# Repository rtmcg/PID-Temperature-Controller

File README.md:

# PHYS-339
Code and hardware schematics for the the new PID temperature controller lab in the Physics 339 laboratory course at McGill university.

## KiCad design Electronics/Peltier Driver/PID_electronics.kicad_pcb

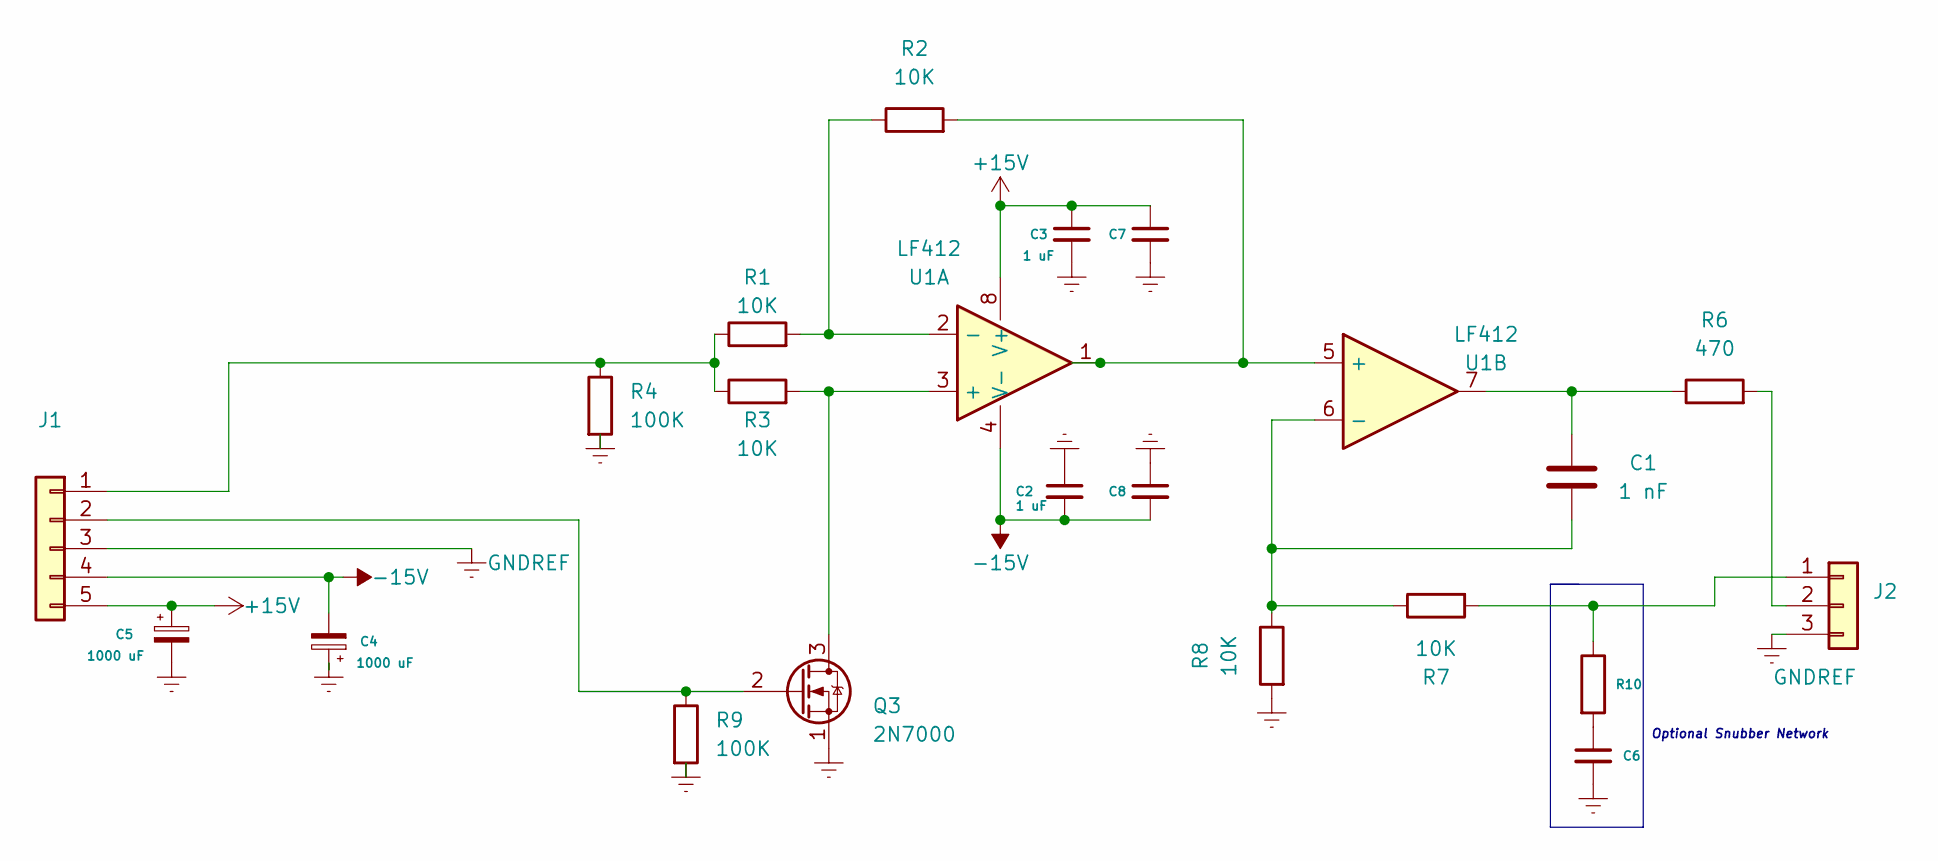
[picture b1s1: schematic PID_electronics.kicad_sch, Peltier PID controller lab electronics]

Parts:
C1: 1 nF; C_Axial_L3.8mm_D2.6mm_P7.50mm_Horizontal
C2, C3: 1 uF; C_Axial_L3.8mm_D2.6mm_P7.50mm_Horizontal
C4, C5: 1000 uF; CP_Radial_D10.0mm_P5.00mm
C6: C_Small; CP_Radial_D10.0mm_P5.00mm
C7, C8: C_Small; C_Axial_L3.8mm_D2.6mm_P7.50mm_Horizontal
J1: Conn_01x05; 1935190
J2: Conn_01x03; 1935174
Q3: 2N7000; TO-92_HandSolder
R1, R2, R3, R7, R8: 10K; R_Axial_DIN0207_L6.3mm_D2.5mm_P10.16mm_Horizontal
R4, R9: 100K; R_Axial_DIN0207_L6.3mm_D2.5mm_P10.16mm_Horizontal
R6: 470; R_Axial_DIN0207_L6.3mm_D2.5mm_P10.16mm_Horizontal
R10: R; R_Axial_DIN0207_L6.3mm_D2.5mm_P10.16mm_Horizontal
U1: LF412; DIP-8_W7.62mm_Socket_LongPads

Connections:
+15V: C3.1, C5.1, C7.1, J1.5, U1.8 (V+)
-15V: C2.2, C4.2, C8.2, J1.4, U1.4 (V-)
GNDREF: C2.1, C3.2, C4.1, C5.2, C6.2, C7.2, C8.1, J1.3, J2.3, Q3.1 (S), R4.2, R8.2, R9.2
unnamed: C1.1, R6.1, U1.7
unnamed: C1.2, R7.1, R8.1, U1.6 (-)
unnamed: J2.1, R7.2, R10.1
unnamed: J2.2, R6.2
unnamed: J1.2, Q3.2 (G), R9.1
unnamed: Q3.3 (D), R3.2, U1.3 (+)
unnamed: J1.1, R1.1, R3.1, R4.1
unnamed: R1.2, R2.1, U1.2 (-)
unnamed: R2.2, U1.1, U1.5 (+)
unnamed: C6.1, R10.2

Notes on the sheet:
Optional Snubber Network

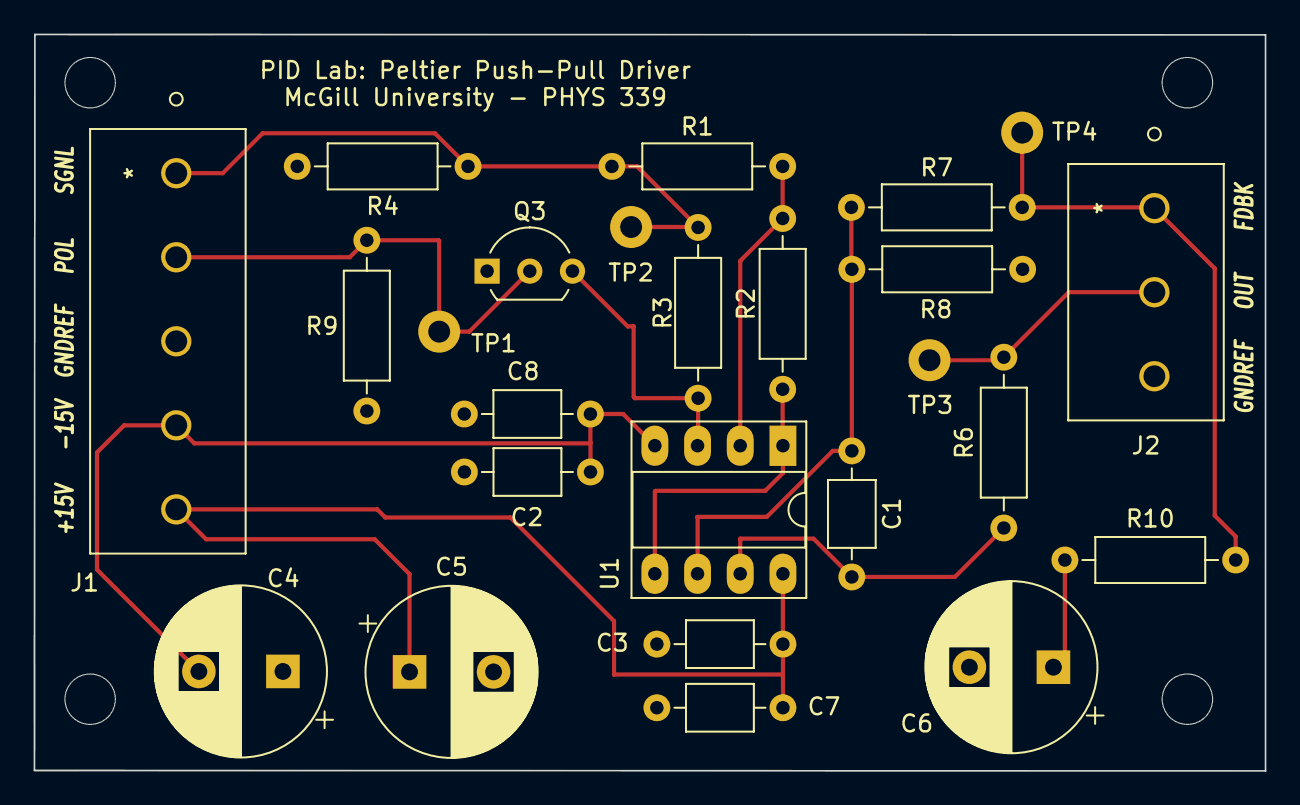
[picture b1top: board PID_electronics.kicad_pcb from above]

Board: 2 copper layers, 73.2 x 43.8 mm, 21 parts (0 on the bottom side), 13 nets.

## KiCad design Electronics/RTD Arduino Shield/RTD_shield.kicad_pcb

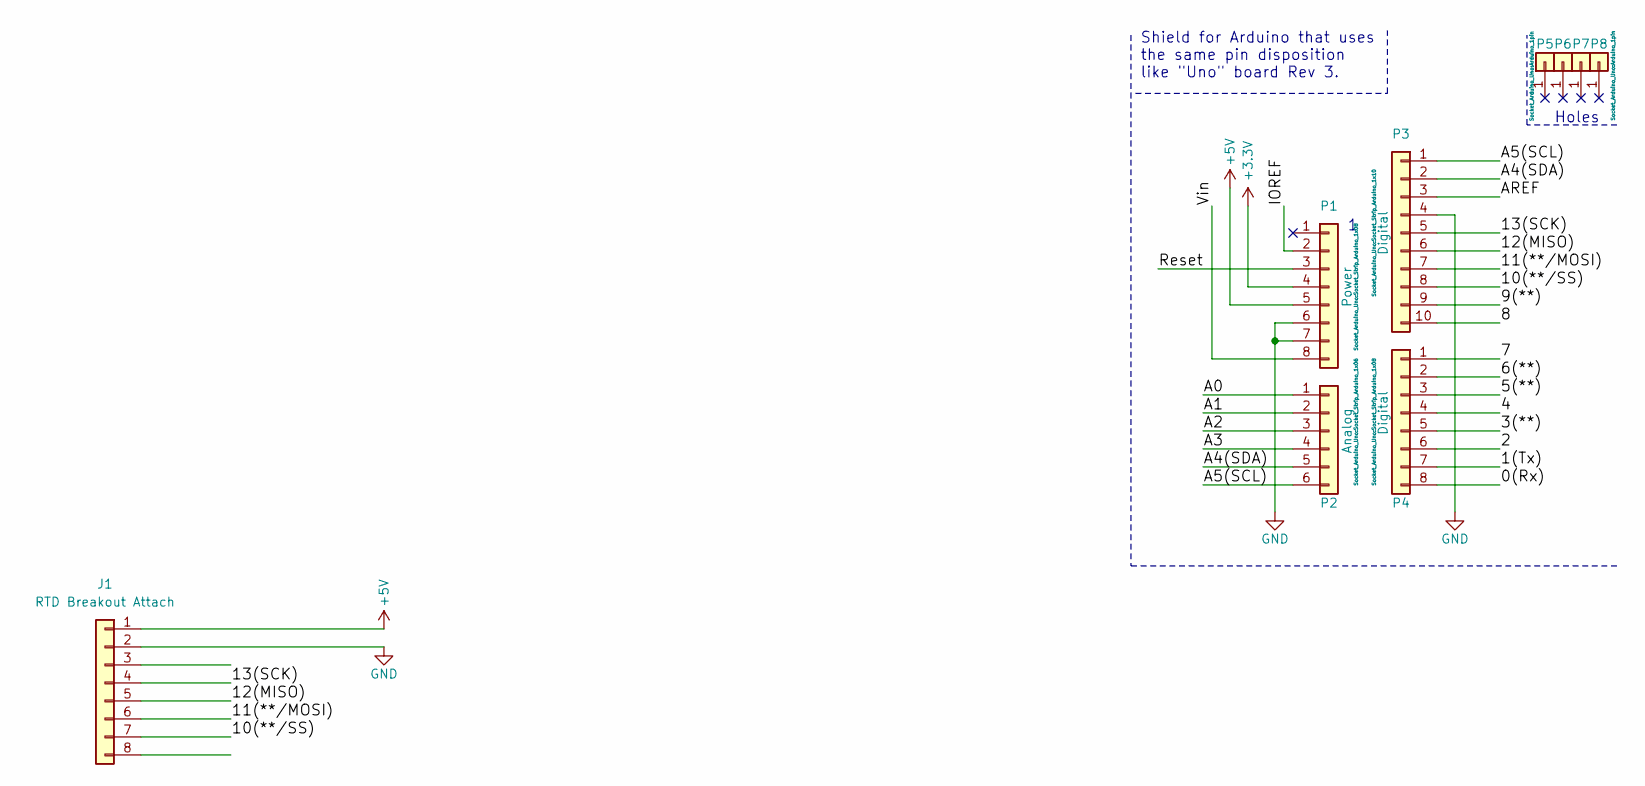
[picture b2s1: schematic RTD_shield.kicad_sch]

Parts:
J1: RTD Breakout Attach; Socket_Strip_Arduino_1x08
P1: Power; Socket_Strip_Arduino_1x08
P2: Analog; Socket_Strip_Arduino_1x06
P3: Digital; Socket_Strip_Arduino_1x10
P4: Digital; Socket_Strip_Arduino_1x08
P5, P6, P7, P8: CONN_01X01; Arduino_1pin

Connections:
+3V3: P1.4
+5V: J1.1, P1.5
/0(Rx): P4.8
/1(Tx): P4.7
/2: P4.6
/3(**): P4.5
/4: P4.4
/5(**): P4.3
/6(**): P4.2
/7: P4.1
/8: P3.10
/9(**): P3.9
/10(**/SS): J1.7, P3.8
/11(**/MOSI): J1.6, P3.7
/12(MISO): J1.5, P3.6
/13(SCK): J1.4, P3.5
/A0: P2.1
/A1: P2.2
/A2: P2.3
/A3: P2.4
/A4(SDA): P2.5, P3.2
/A5(SCL): P2.6, P3.1
/AREF: P3.3
/IOREF: P1.2
/Reset: P1.3
/Vin: P1.8
GND: J1.2, P1.6, P1.7, P3.4

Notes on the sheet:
Holes
Shield for Arduino that uses the same pin disposition like "Uno" board Rev 3.

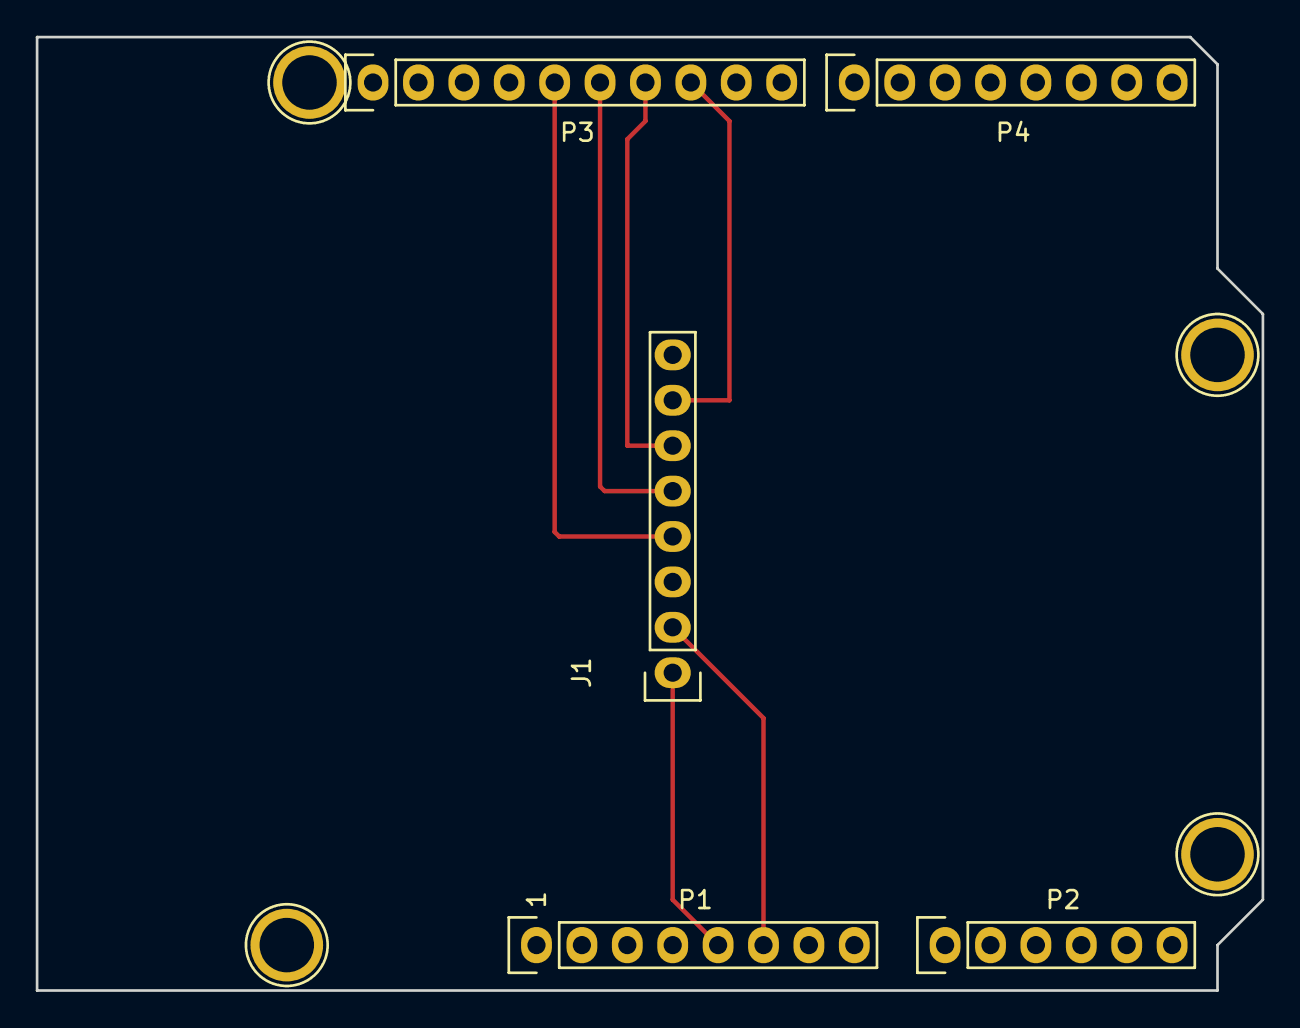
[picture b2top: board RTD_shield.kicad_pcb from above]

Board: 2 copper layers, 68.6 x 53.3 mm, 9 parts (0 on the bottom side), 8 nets.

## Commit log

2021-09-30 Improving Documentation and removing redundancy
2021-09-30 File change
2021-09-30 Deleted a file
2021-09-30 Fixed data line problems, improved debug
2021-10-07 small changes
2021-10-13 Removing old code for a new implementation
2021-10-13 New implementation of arduino api and GUI based on mcphysics auber controller.
2021-10-13 Arduino Code begins
2021-10-13 Adding serial functionality
2021-10-13 Adding functionality
2021-10-14 Integrating arduino code and python api.
2021-10-14 minor changes
2021-10-14 Fixing problems and adding functionality to all program components
2021-10-18 Fixed simulation in the GUI
2021-10-18 broad additions
2021-10-29 Api and arduino code fixes
2021-11-11 Major updates across the board
2021-11-18 Added functionality on both GUI and arduino side.
2021-11-19 breaking up arduino.py
2021-11-19 Broke up arduino.py into api and gui scripts.
2021-11-19 Moving toward a functioning version
2021-11-19 Modifed read_temperature()
2021-11-29 Added RTD temperature measurement (MAX31865 ic)
2021-12-02 Stable in open and closed loop operation.
2021-12-03 Added functionality for changing control period from gui and a single function to get all parameters from arduino to the api (get_all_variables) to simplify querying of the arduino.
2021-12-03 minor updates
2021-12-07 Added variables and math for calculating dt, the time differential needed for the control function.
2021-12-07 Removed the GUI window population code from init to clean up the code, added provision from automatically finding arduino serial port.
2022-01-11 CAD files for supporting electronics
2022-01-12 Test Arduino shield for RTD breakout board
2022-01-12 Terminal block footprints
2022-01-12 File reorganization
2022-01-12 File reorg
2022-01-12 photos for the wiki
2022-01-12 photos
2022-01-13 Combined schematic of 3 electronics blocks
2022-01-13 Combined schematic of 3 electronics blocks (minor change)
2022-01-14 updated silkscreen
2022-01-14 Components for PCB construction
2022-01-14 schematic image added
2022-01-14 Gerber files for PCB production
2022-01-20 Image of data acquisition in the gui added
2022-01-21 Added mounting holes
2022-01-21 mounting hole footprint
2022-01-24 Board revision
2022-01-31 Added Bulk decoupling capacitors and optional snubber network
2022-02-01 Have to add changes
2022-02-01 Added additional optional bypass capacitors
2022-02-01 Replaced Opamp footprint with socket footprint
2022-02-02 Changed default BAUD to 115200
2022-02-02 Added test points, changed 2n7000 T0-92 footprint
2022-02-03 Layout optimization, mounting hole addition
2022-02-03 2N7000 footprint change, gerbers generated
2022-02-03 minor layout change
2022-02-15 Schematic PDF
2022-02-28 Added text indicator on disconnect
2022-02-28 Added feature to refresh serial port list in GUI
2022-03-11 Changed Polarity and RTD module pin assignments foruse in 339 labs
2022-03-21 Commented .py and .ino files. MAX38165 pin assignments
    Added introductory comments with authorship and accompanying script names in .py and .ino files.
    Corrected MAX38165 pin assignments in .ino code.

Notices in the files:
parts and their libraries:
Copyright 2021 Accelerated Designs. All rights reserved.
